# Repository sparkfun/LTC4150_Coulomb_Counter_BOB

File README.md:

SparkFun Coulomb Counter Breakout - LTC4150
===========================

[![SparkFun Coulomb Counter Breakout - LTC4150
](https://cdn.sparkfun.com//assets/parts/8/6/3/7/12052-01.jpg)](https://www.sparkfun.com/products/12052)

_[SparkFun Coulomb Counter Breakout - LTC4150 [ BOB-12052 ]](https://www.sparkfun.com/products/12052)_

*Breakout board for the Linear Tech LTC4150 Coulomb Counter (bidirectional current sensor / battery gauge)*

The LTC4150 Coulomb Counter monitors current passing through it (from the IN header or JST connector to the OUT header). Each time 0.1707 mAh passes through the device, the INT pin will pulse low. Or to put it another way, the INT pin will pulse low 5859 times for each Ah that passes through it.

There is also a POL pin that you can check each time INT goes low. POL will be L for current going from IN to OUT, and H for current going from OUT to IN (battery charging).

If you count these pulses and add or subtract from a total depending on the POL signal, you can keep accurate track of the state of a battery connected to the board.

The Coulomb Counter can accommodate power supplies up to 8.5V and up to 1A.

Quickstart (Arduino)
-------------------

* Configure the jumpers:

    If you're connecting the Coulomb Counter to a 5V system, leave solder jumpers SJ2 and SJ3 (on the bottom of the board) open (the default).

    If you're connecting the Coulomb Counter to a 3.3V system, close both SJ2 and SJ3.

* Hook up the I/O lines:

    Connect VIO to your system's VCC (3.3V or 5V) line.

    Connect GND to your system's ground line.

    Connect INT to your system's interrupt input (D3)

    Connect POL to an I/O pin (D4)

* Connect the IN header or the JST connector to your power source (up to 8.5V)

* Connect the OUT header to your system's power input

* Upload and run the Coulomb_Interrupt example code from this repository, and open a Serial Monitor set to 9600 bps. It should display a hello message and begin giving you periodic updates about the battery state. (See the comments for instructions on customizing it for your exact battery.)

See the [Hookup Guide](https://learn.sparkfun.com/tutorials/ltc4150-coulomb-counter-hookup-guide) for much more information.

Have fun! -Your friends at SparkFun

Repository Contents
-------------------

* **/Documentation** - Data sheets, additional product information
* **/Hardware** - Eagle design files (.brd, .sch)
* **/Production** - Production panel files (.brd)
* **/Software** - Arduino example code

Documentation
--------------

* **[Hookup Guide](https://learn.sparkfun.com/tutorials/ltc4150-coulomb-counter-hookup-guide)** - Basic hookup guide

License Information
-------------------

This product is _**open source**_! 

Please review the LICENSE.md file for license information. 

If you have any questions or concerns on licensing, please contact technical support on our [SparkFun forums](https://forum.sparkfun.com/viewforum.php?f=152).

Distributed as-is; no warranty is given.

- Your friends at SparkFun.

_<COLLABORATION CREDIT>_

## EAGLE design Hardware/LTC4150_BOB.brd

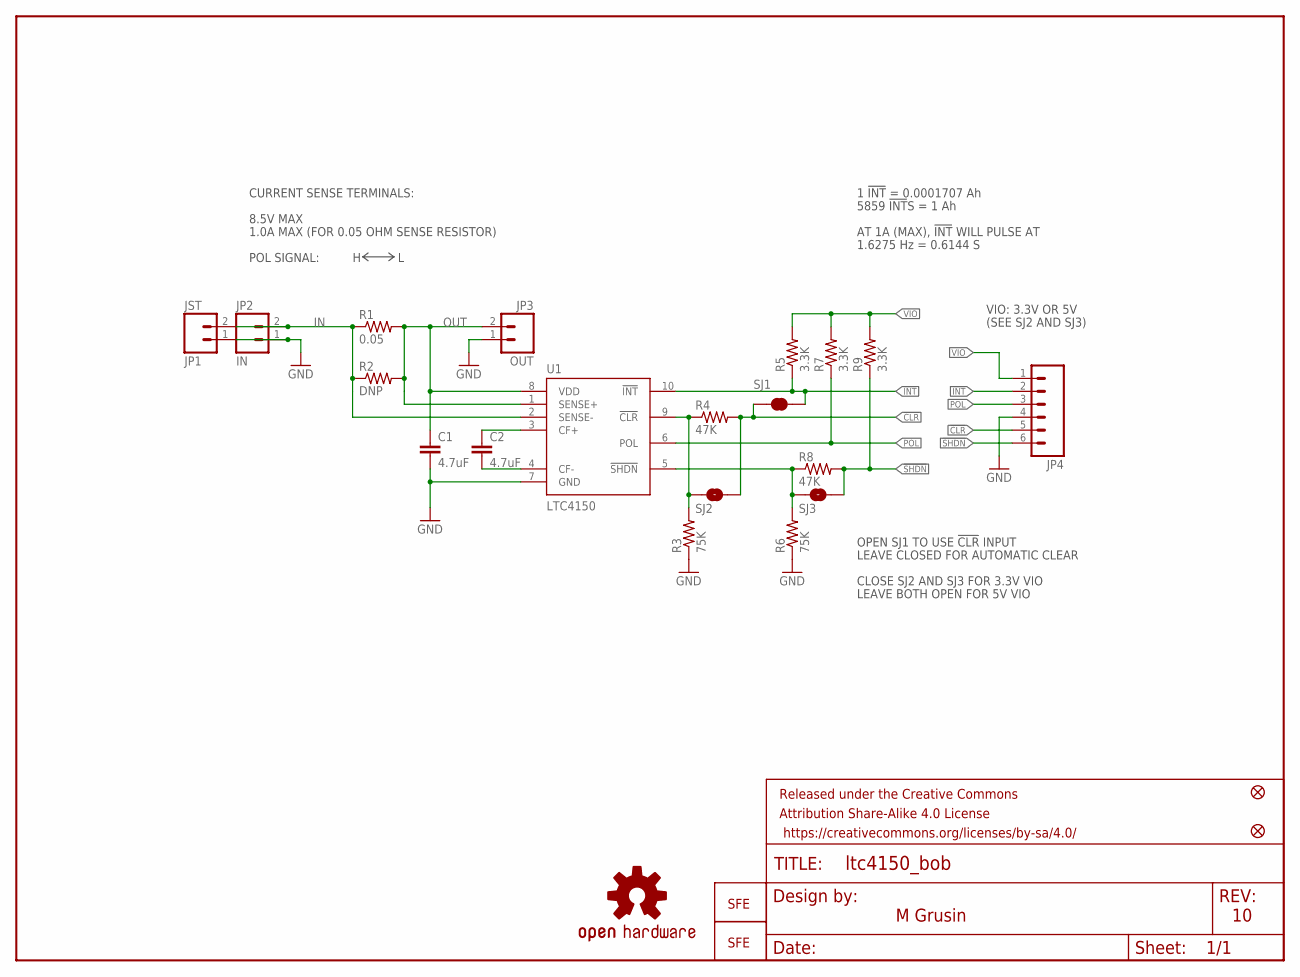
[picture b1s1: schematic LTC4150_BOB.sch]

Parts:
C1, C2: 4.7uF; 0603-CAP
FID1, FID2: FIDUCIAL1X2; FIDUCIAL-1X2
FRAME1: FRAME-LETTER; CREATIVE_COMMONS
JP1: JST; JST-2-SMD
JP2: IN; 1X02
JP3: OUT; 1X02
JP4: M06SIP; 1X06
LOGO1: OSHW-LOGOS; OSHW-LOGO-S
LOGO2: LOGO-SFENW2; SFE-NEW-WEB
LOGO3: LOGO-SFESK; SFE-LOGO-FLAME
R1: 0.05; 1206
R2: DNP; AXIAL-0.3
R3, R6: 75K; 0603-RES
R4, R8: 47K; 0603-RES
R5, R7, R9: 3.3K; 0603-RES
SJ1: SOLDERJUMPERNC; SJ_2S
SJ2, SJ3: SOLDERJUMPERNO; SJ_2S-NO
U1: LTC4150; MSOP10

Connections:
!CLR!: JP4.5, R4.2, SJ1.1, SJ2.2
!INT!: JP4.2, R5.1, SJ1.2, U1.10 (!INT!)
!SHDN!: JP4.6, R8.2, R9.1, SJ3.2
GND: C1.2, JP1.1 (2), JP2.1, JP3.1, JP4.4, R3.1, R6.1, U1.7 (GND)
IN: JP1.2 (1), JP2.2, R1.1, R2.P$1 (1), U1.2 (SENSE-)
unnamed: R3.2, R4.1, SJ2.1, U1.9 (!CLR!)
unnamed: C2.1, U1.3 (CF+)
unnamed: C2.2, U1.4 (CF-)
unnamed: R6.2, R8.1, SJ3.1, U1.5 (!SHDN!)
OUT: C1.1, JP3.2, R1.2, R2.P$2 (2), U1.1 (SENSE+), U1.8 (VDD)
POL: JP4.3, R7.1, U1.6 (POL)
VIO: JP4.1, R5.2, R7.2, R9.2

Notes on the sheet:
M Grusin
CLOSE SJ2 AND SJ3 FOR 3.3V VIO
CURRENT SENSE TERMINALS:
LEAVE BOTH OPEN FOR 5V VIO
AT 1A (MAX), !INT! WILL PULSE AT
1.6275 Hz = 0.6144 S
1 !INT! = 0.0001707 Ah
5859 !INT!S = 1 Ah
OPEN SJ1 TO USE !CLR! INPUT
1.0A MAX (FOR 0.05 OHM SENSE RESISTOR)
VIO: 3.3V OR 5V
(SEE SJ2 AND SJ3)
LEAVE CLOSED FOR AUTOMATIC CLEAR
8.5V MAX
POL SIGNAL:

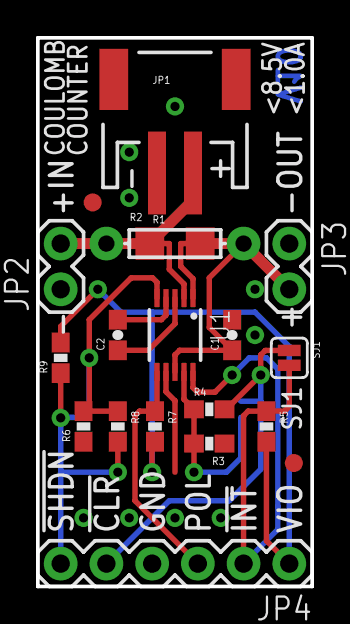
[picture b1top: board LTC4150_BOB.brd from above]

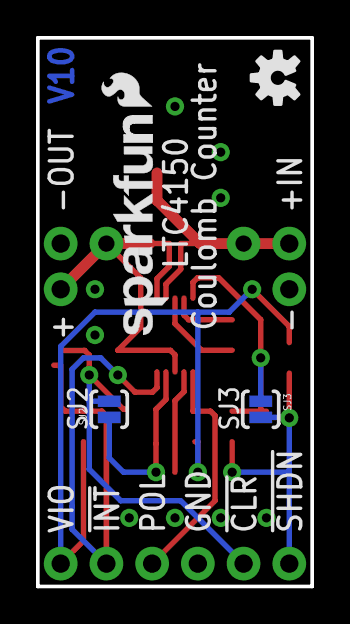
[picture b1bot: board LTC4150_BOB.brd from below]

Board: 2 copper layers, 15.2 x 30.5 mm, 25 parts (5 on the bottom side), 12 nets.

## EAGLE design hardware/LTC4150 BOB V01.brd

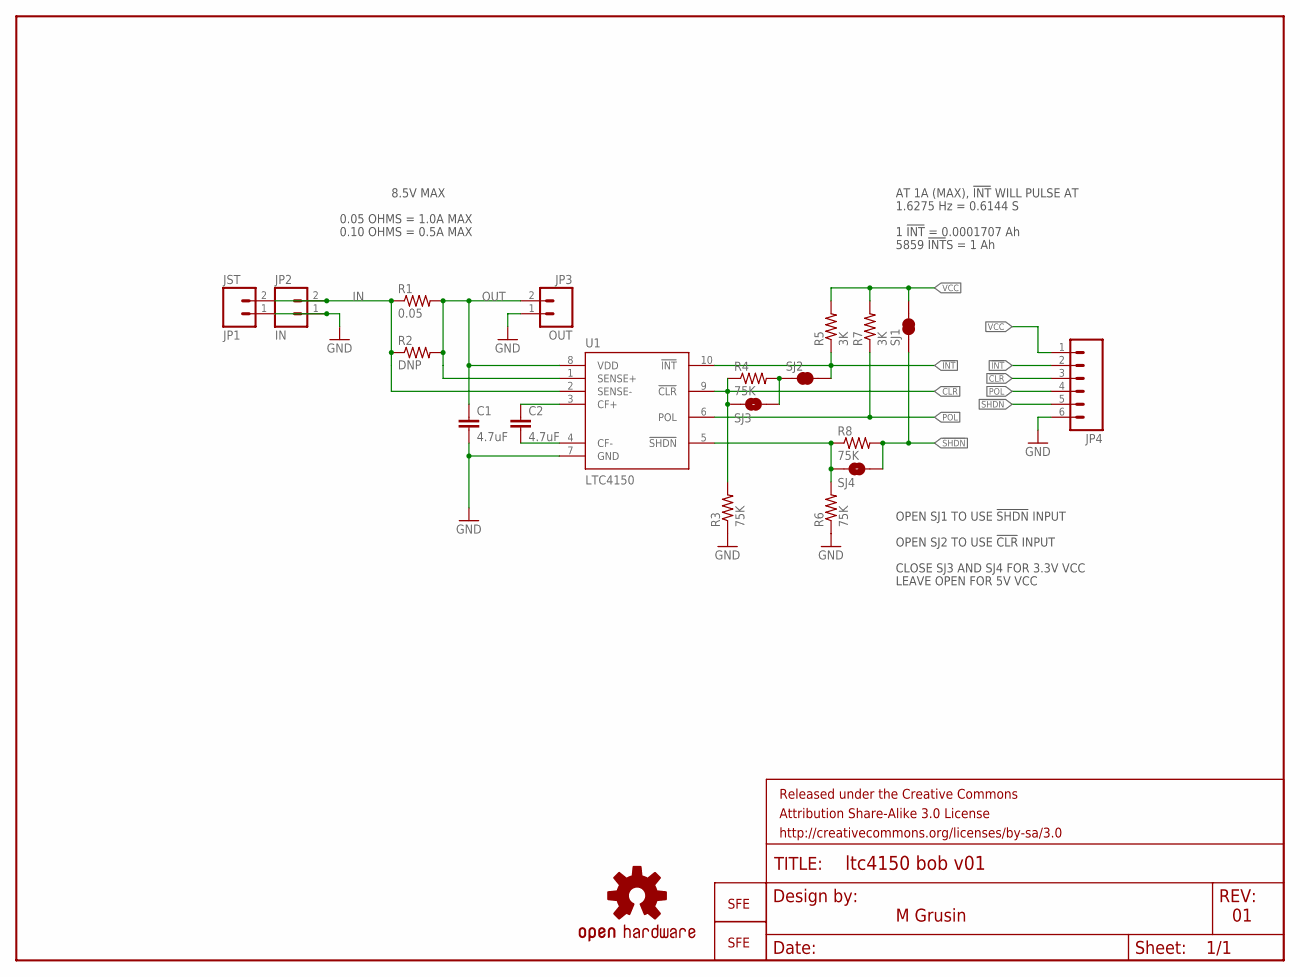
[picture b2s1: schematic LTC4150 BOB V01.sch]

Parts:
C1, C2: 4.7uF; 0603-CAP
FRAME1: FRAME-LETTER; CREATIVE_COMMONS
JP1: JST; JST-2-SMD
JP2: IN; 1X02
JP3: OUT; 1X02
JP4: M06SIP; 1X06
LOGO1: OSHW-LOGOS; OSHW-LOGO-S
LOGO2: LOGO-SFENW2; SFE-NEW-WEB
LOGO3: LOGO-SFESK; SFE-LOGO-FLAME
R1: 0.05; 0805
R2: DNP; AXIAL-0.3
R3, R4, R6, R8: 75K; 0603-RES
R5, R7: 3K; 0603-RES
SJ1, SJ2: SOLDERJUMPERNC; SJ_2S
SJ3, SJ4: SOLDERJUMPERNO; SJ_2S-NO
U1: LTC4150; MSOP10

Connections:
!CLR!: JP4.3, R3.2, R4.1, SJ3.1, U1.9 (!CLR!)
!INT!: JP4.2, R5.1, SJ2.2, U1.10 (!INT!)
!SHDN!: JP4.5, R8.2, SJ1.2, SJ4.2
GND: C1.2, JP1.1 (2), JP2.1, JP3.1, JP4.6, R3.1, R6.1, U1.7 (GND)
IN: JP1.2 (1), JP2.2, R1.1, R2.P$1 (1), U1.2 (SENSE-)
unnamed: R4.2, SJ2.1, SJ3.2
unnamed: C2.1, U1.3 (CF+)
unnamed: C2.2, U1.4 (CF-)
unnamed: R6.2, R8.1, SJ4.1, U1.5 (!SHDN!)
OUT: C1.1, JP3.2, R1.2, R2.P$2 (2), U1.1 (SENSE+), U1.8 (VDD)
POL: JP4.4, R7.1, U1.6 (POL)
VCC: JP4.1, R5.2, R7.2, SJ1.1

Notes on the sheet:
M Grusin
CLOSE SJ3 AND SJ4 FOR 3.3V VCC
OPEN SJ1 TO USE !SHDN! INPUT
8.5V MAX
LEAVE OPEN FOR 5V VCC
AT 1A (MAX), !INT! WILL PULSE AT
1.6275 Hz = 0.6144 S
1 !INT! = 0.0001707 Ah
5859 !INT!S = 1 Ah
OPEN SJ2 TO USE !CLR! INPUT
0.05 OHMS = 1.0A MAX
0.10 OHMS = 0.5A MAX

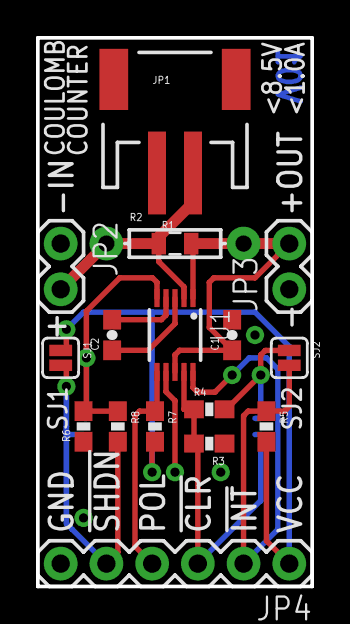
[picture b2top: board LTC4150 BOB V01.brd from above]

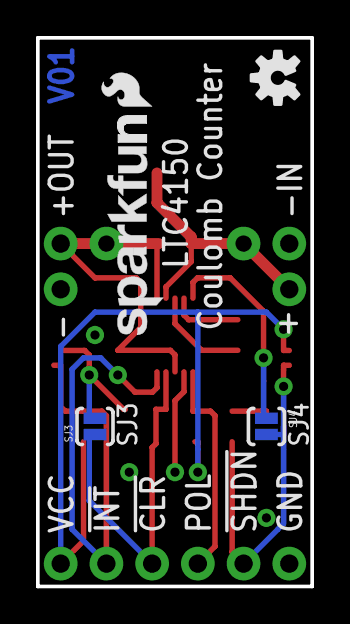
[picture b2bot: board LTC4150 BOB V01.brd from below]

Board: 2 copper layers, 15.2 x 30.5 mm, 23 parts (5 on the bottom side), 12 nets.

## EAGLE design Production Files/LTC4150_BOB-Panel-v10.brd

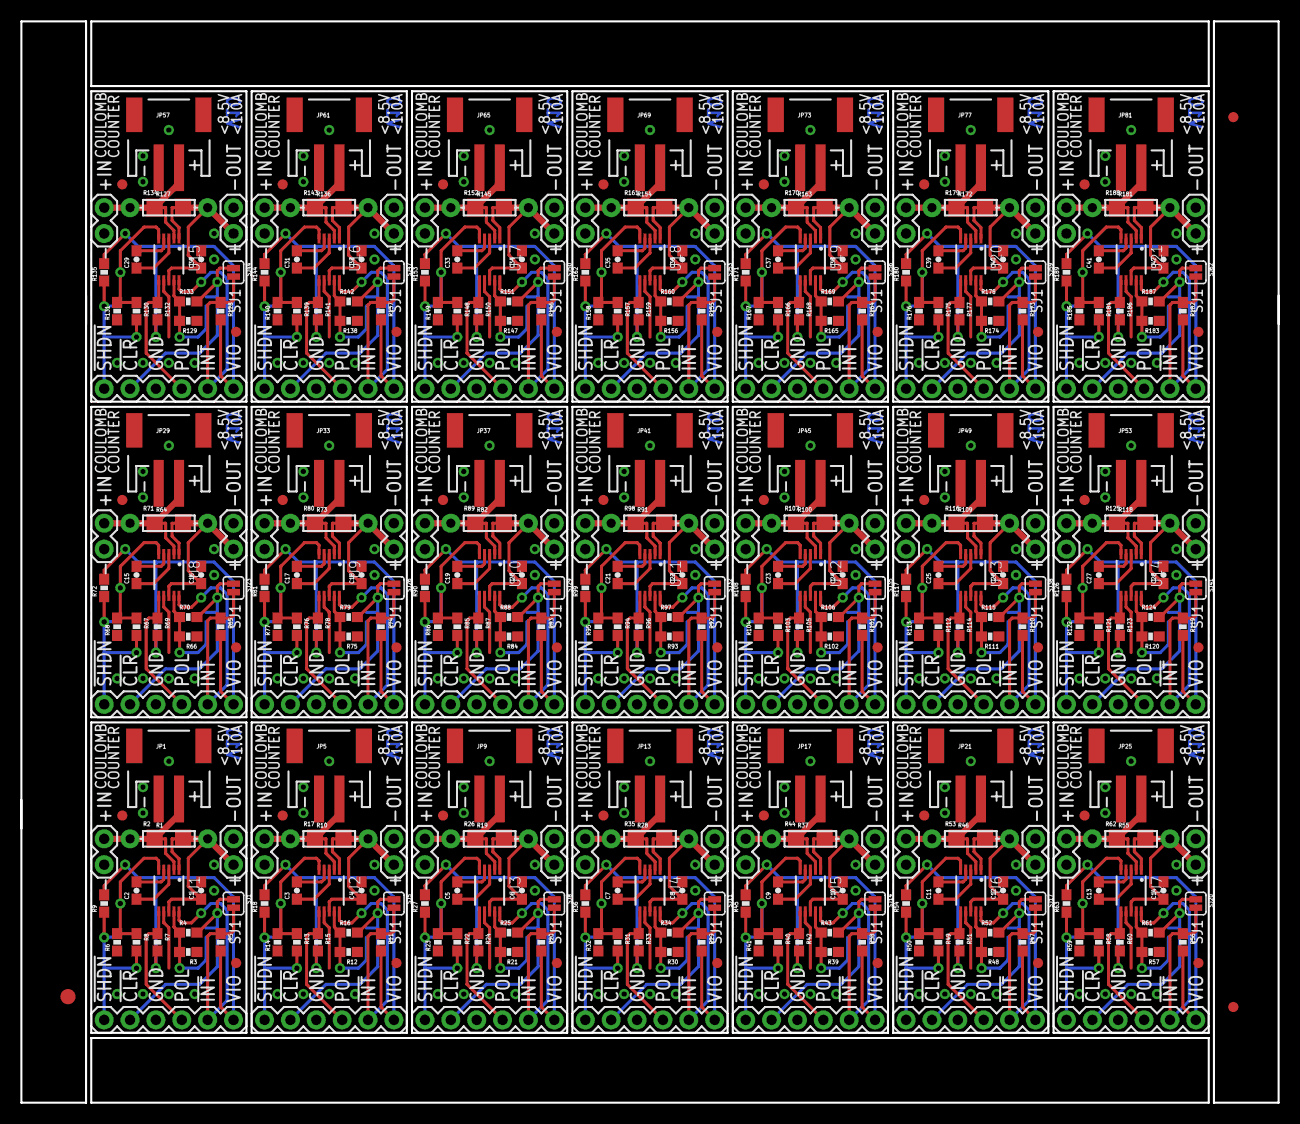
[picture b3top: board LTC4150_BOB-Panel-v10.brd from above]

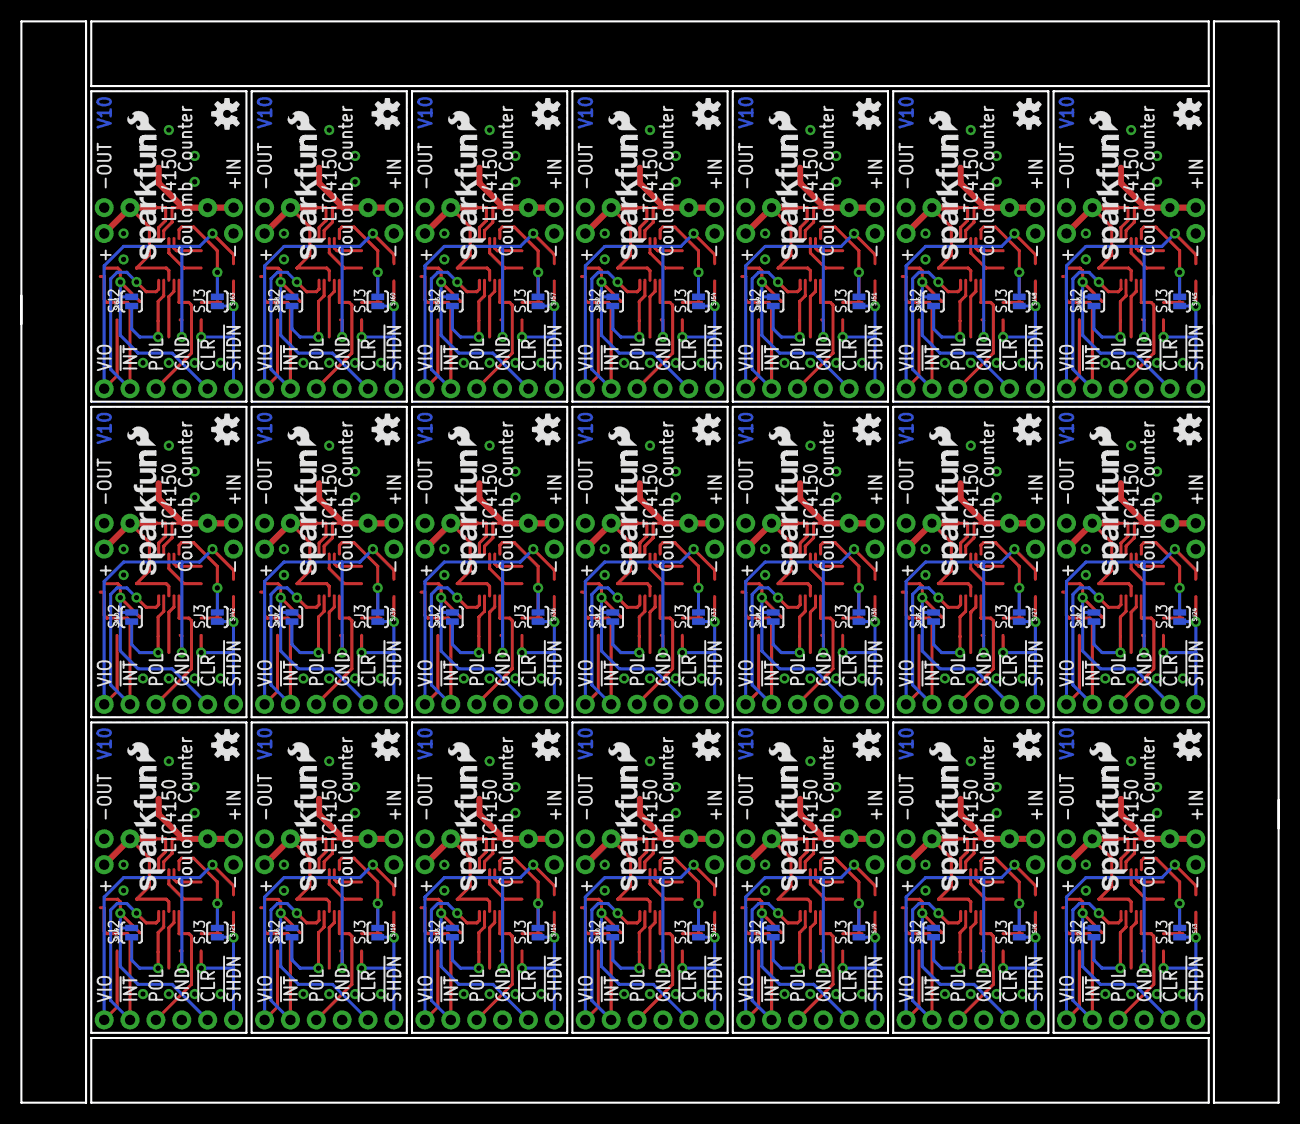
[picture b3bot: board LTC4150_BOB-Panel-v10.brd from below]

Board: 2 copper layers, 123.4 x 106.2 mm, 507 parts (105 on the bottom side), 252 nets.

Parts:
C1, C2, C3, C4, C5, C6, C7, C8, C9, C10, C11, C12, C13, C14, C15, C16, C17, C18, C19, C20, C21, C22, C23, C24, C25, C26, C27, C28, C29, C30, C31, C32, C33, C34, C35, C36, C37, C38, C39, C40, C41, C42: 4.7uF; 0603-CAP
E$1: FIDUCIAL-1.5X3
E$4, E$5: FIDUCIAL-1X2
FID1, FID2, FID3, FID4, FID5, FID6, FID7, FID8, FID9, FID10, FID11, FID12, FID13, FID14, FID15, FID16, FID17, FID18, FID19, FID20, FID21, FID22, FID23, FID24, FID25, FID26, FID27, FID28, FID29, FID30, FID31, FID32, FID33, FID34, FID35, FID36, FID37, FID38, FID39, FID40, FID41, FID42: FIDUCIAL1X2; FIDUCIAL-1X2
JP1, JP5, JP9, JP13, JP17, JP21, JP25, JP29, JP33, JP37, JP41, JP45, JP49, JP53, JP57, JP61, JP65, JP69, JP73, JP77, JP81: JST; JST-2-SMD
JP2, JP6, JP10, JP14, JP18, JP22, JP26, JP30, JP34, JP38, JP42, JP46, JP50, JP54, JP58, JP62, JP66, JP70, JP74, JP78, JP82: IN; 1X02
JP3, JP7, JP11, JP15, JP19, JP23, JP27, JP31, JP35, JP39, JP43, JP47, JP51, JP55, JP59, JP63, JP67, JP71, JP75, JP79, JP83: OUT; 1X02
JP4, JP8, JP12, JP16, JP20, JP24, JP28, JP32, JP36, JP40, JP44, JP48, JP52, JP56, JP60, JP64, JP68, JP72, JP76, JP80, JP84: 1X06
LOGO1, LOGO5, LOGO8, LOGO11, LOGO14, LOGO17, LOGO20, LOGO23, LOGO26, LOGO29, LOGO32, LOGO35, LOGO38, LOGO41, LOGO44, LOGO47, LOGO50, LOGO53, LOGO56, LOGO59, LOGO62: OSHW-LOGOS; OSHW-LOGO-S
LOGO2, LOGO6, LOGO9, LOGO12, LOGO15, LOGO18, LOGO21, LOGO24, LOGO27, LOGO30, LOGO33, LOGO36, LOGO39, LOGO42, LOGO45, LOGO48, LOGO51, LOGO54, LOGO57, LOGO60, LOGO63: LOGO-SFENW2; SFE-NEW-WEB
LOGO3, LOGO4, LOGO7, LOGO10, LOGO13, LOGO16, LOGO19, LOGO22, LOGO25, LOGO28, LOGO31, LOGO34, LOGO37, LOGO40, LOGO43, LOGO46, LOGO49, LOGO52, LOGO55, LOGO58, LOGO61: LOGO-SFESK; SFE-LOGO-FLAME
R1, R10, R19, R28, R37, R46, R55, R64, R73, R82, R91, R100, R109, R118, R127, R136, R145, R154, R163, R172, R181: 0.05; 1206
R2, R17, R26, R35, R44, R53, R62, R71, R80, R89, R98, R107, R116, R125, R134, R143, R152, R161, R170, R179, R188: DNP; AXIAL-0.3
R3, R6, R12, R14, R21, R23, R30, R32, R39, R41, R48, R50, R57, R59, R66, R68, R75, R77, R84, R86, R93, R95, R102, R104, R111, R113, R120, R122, R129, R131, R138, R140, R147, R149, R156, R158, R165, R167, R174, R176, R183, R185: 75K; 0603-RES
R4, R8, R13, R16, R22, R25, R31, R34, R40, R43, R49, R52, R58, R61, R67, R70, R76, R79, R85, R88, R94, R97, R103, R106, R112, R115, R121, R124, R130, R133, R139, R142, R148, R151, R157, R160, R166, R169, R175, R178, R184, R187: 47K; 0603-RES
R5, R7, R9, R11, R15, R18, R20, R24, R27, R29, R33, R36, R38, R42, R45, R47, R51, R54, R56, R60, R63, R65, R69, R72, R74, R78, R81, R83, R87, R90, R92, R96, R99, R101, R105, R108, R110, R114, R117, R119, R123, R126, R128, R132, R135, R137, R141, R144, R146, R150, R153, R155, R159, R162, R164, R168, R171, R173, R177, R180, R182, R186, R189: 3.3K; 0603-RES
SJ1, SJ5, SJ8, SJ11, SJ14, SJ17, SJ20, SJ23, SJ26, SJ29, SJ32, SJ35, SJ38, SJ41, SJ44, SJ47, SJ50, SJ53, SJ56, SJ59, SJ62: SJ_2S
SJ2, SJ3, SJ4, SJ6, SJ7, SJ9, SJ10, SJ12, SJ13, SJ15, SJ16, SJ18, SJ19, SJ21, SJ22, SJ24, SJ25, SJ27, SJ28, SJ30, SJ31, SJ33, SJ34, SJ36, SJ37, SJ39, SJ40, SJ42, SJ43, SJ45, SJ46, SJ48, SJ49, SJ51, SJ52, SJ54, SJ55, SJ57, SJ58, SJ60, SJ61, SJ63: SJ_2S-NO
U1, U2, U3, U4, U5, U6, U7, U8, U9, U10, U11, U12, U13, U14, U15, U16, U17, U18, U19, U20, U21: LTC4150; MSOP10

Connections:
!CLR!: JP4.5, R4.2, SJ1.1, SJ2.2
!CLR!1: JP8.5, R16.2, SJ4.2, SJ5.1
!CLR!2: JP12.5, R25.2, SJ7.2, SJ8.1
!CLR!3: JP16.5, R34.2, SJ10.2, SJ11.1
!CLR!4: JP20.5, R43.2, SJ13.2, SJ14.1
!CLR!5: JP24.5, R52.2, SJ16.2, SJ17.1
!CLR!6: JP28.5, R61.2, SJ19.2, SJ20.1
!CLR!7: JP32.5, R70.2, SJ22.2, SJ23.1
!CLR!8: JP36.5, R79.2, SJ25.2, SJ26.1
!CLR!9: JP40.5, R88.2, SJ28.2, SJ29.1
!CLR!10: JP44.5, R97.2, SJ31.2, SJ32.1
!CLR!11: JP48.5, R106.2, SJ34.2, SJ35.1
!CLR!12: JP52.5, R115.2, SJ37.2, SJ38.1
!CLR!13: JP56.5, R124.2, SJ40.2, SJ41.1
!CLR!14: JP60.5, R133.2, SJ43.2, SJ44.1
!CLR!15: JP64.5, R142.2, SJ46.2, SJ47.1
!CLR!16: JP68.5, R151.2, SJ49.2, SJ50.1
!CLR!17: JP72.5, R160.2, SJ52.2, SJ53.1
!CLR!18: JP76.5, R169.2, SJ55.2, SJ56.1
!CLR!19: JP80.5, R178.2, SJ58.2, SJ59.1
!CLR!20: JP84.5, R187.2, SJ61.2, SJ62.1
!INT!: JP4.2, R5.1, SJ1.2, U1.10
!INT!1: JP8.2, R11.1, SJ5.2, U2.10
!INT!2: JP12.2, R20.1, SJ8.2, U3.10
!INT!3: JP16.2, R29.1, SJ11.2, U4.10
!INT!4: JP20.2, R38.1, SJ14.2, U5.10
!INT!5: JP24.2, R47.1, SJ17.2, U6.10
!INT!6: JP28.2, R56.1, SJ20.2, U7.10
!INT!7: JP32.2, R65.1, SJ23.2, U8.10
!INT!8: JP36.2, R74.1, SJ26.2, U9.10
!INT!9: JP40.2, R83.1, SJ29.2, U10.10
!INT!10: JP44.2, R92.1, SJ32.2, U11.10
!INT!11: JP48.2, R101.1, SJ35.2, U12.10
!INT!12: JP52.2, R110.1, SJ38.2, U13.10
!INT!13: JP56.2, R119.1, SJ41.2, U14.10
!INT!14: JP60.2, R128.1, SJ44.2, U15.10
!INT!15: JP64.2, R137.1, SJ47.2, U16.10
!INT!16: JP68.2, R146.1, SJ50.2, U17.10
!INT!17: JP72.2, R155.1, SJ53.2, U18.10
!INT!18: JP76.2, R164.1, SJ56.2, U19.10
!INT!19: JP80.2, R173.1, SJ59.2, U20.10
!INT!20: JP84.2, R182.1, SJ62.2, U21.10
!SHDN!: JP4.6, R8.2, R9.1, SJ3.2
!SHDN!1: JP8.6, R13.2, R18.1, SJ6.2
!SHDN!2: JP12.6, R22.2, R27.1, SJ9.2
!SHDN!3: JP16.6, R31.2, R36.1, SJ12.2
!SHDN!4: JP20.6, R40.2, R45.1, SJ15.2
!SHDN!5: JP24.6, R49.2, R54.1, SJ18.2
!SHDN!6: JP28.6, R58.2, R63.1, SJ21.2
!SHDN!7: JP32.6, R67.2, R72.1, SJ24.2
!SHDN!8: JP36.6, R76.2, R81.1, SJ27.2
!SHDN!9: JP40.6, R85.2, R90.1, SJ30.2
!SHDN!10: JP44.6, R94.2, R99.1, SJ33.2
!SHDN!11: JP48.6, R103.2, R108.1, SJ36.2
!SHDN!12: JP52.6, R112.2, R117.1, SJ39.2
!SHDN!13: JP56.6, R121.2, R126.1, SJ42.2
!SHDN!14: JP60.6, R130.2, R135.1, SJ45.2
!SHDN!15: JP64.6, R139.2, R144.1, SJ48.2
!SHDN!16: JP68.6, R148.2, R153.1, SJ51.2
!SHDN!17: JP72.6, R157.2, R162.1, SJ54.2
!SHDN!18: JP76.6, R166.2, R171.1, SJ57.2
!SHDN!19: JP80.6, R175.2, R180.1, SJ60.2
!SHDN!20: JP84.6, R184.2, R189.1, SJ63.2
GND: C1.2, JP1.1, JP2.1, JP3.1, JP4.4, R3.1, R6.1, U1.7
GND1: C4.2, JP5.1, JP6.1, JP7.1, JP8.4, R12.1, R14.1, U2.7
GND2: C6.2, JP9.1, JP10.1, JP11.1, JP12.4, R21.1, R23.1, U3.7
GND3: C8.2, JP13.1, JP14.1, JP15.1, JP16.4, R30.1, R32.1, U4.7
GND4: C10.2, JP17.1, JP18.1, JP19.1, JP20.4, R39.1, R41.1, U5.7
GND5: C12.2, JP21.1, JP22.1, JP23.1, JP24.4, R48.1, R50.1, U6.7
GND6: C14.2, JP25.1, JP26.1, JP27.1, JP28.4, R57.1, R59.1, U7.7
GND7: C16.2, JP29.1, JP30.1, JP31.1, JP32.4, R66.1, R68.1, U8.7
GND8: C18.2, JP33.1, JP34.1, JP35.1, JP36.4, R75.1, R77.1, U9.7
GND9: C20.2, JP37.1, JP38.1, JP39.1, JP40.4, R84.1, R86.1, U10.7
GND10: C22.2, JP41.1, JP42.1, JP43.1, JP44.4, R93.1, R95.1, U11.7
GND11: C24.2, JP45.1, JP46.1, JP47.1, JP48.4, R102.1, R104.1, U12.7
GND12: C26.2, JP49.1, JP50.1, JP51.1, JP52.4, R111.1, R113.1, U13.7
GND13: C28.2, JP53.1, JP54.1, JP55.1, JP56.4, R120.1, R122.1, U14.7
GND14: C30.2, JP57.1, JP58.1, JP59.1, JP60.4, R129.1, R131.1, U15.7
GND15: C32.2, JP61.1, JP62.1, JP63.1, JP64.4, R138.1, R140.1, U16.7
GND16: C34.2, JP65.1, JP66.1, JP67.1, JP68.4, R147.1, R149.1, U17.7
GND17: C36.2, JP69.1, JP70.1, JP71.1, JP72.4, R156.1, R158.1, U18.7
GND18: C38.2, JP73.1, JP74.1, JP75.1, JP76.4, R165.1, R167.1, U19.7
GND19: C40.2, JP77.1, JP78.1, JP79.1, JP80.4, R174.1, R176.1, U20.7
GND20: C42.2, JP81.1, JP82.1, JP83.1, JP84.4, R183.1, R185.1, U21.7
IN: JP1.2, JP2.2, R1.1, R2.P$1, U1.2
IN1: JP5.2, JP6.2, R10.1, R17.P$1, U2.2
IN2: JP9.2, JP10.2, R19.1, R26.P$1, U3.2
IN3: JP13.2, JP14.2, R28.1, R35.P$1, U4.2
IN4: JP17.2, JP18.2, R37.1, R44.P$1, U5.2
IN5: JP21.2, JP22.2, R46.1, R53.P$1, U6.2
IN6: JP25.2, JP26.2, R55.1, R62.P$1, U7.2
IN7: JP29.2, JP30.2, R64.1, R71.P$1, U8.2
IN8: JP33.2, JP34.2, R73.1, R80.P$1, U9.2
IN9: JP37.2, JP38.2, R82.1, R89.P$1, U10.2
IN10: JP41.2, JP42.2, R91.1, R98.P$1, U11.2
IN11: JP45.2, JP46.2, R100.1, R107.P$1, U12.2
IN12: JP49.2, JP50.2, R109.1, R116.P$1, U13.2
IN13: JP53.2, JP54.2, R118.1, R125.P$1, U14.2
IN14: JP57.2, JP58.2, R127.1, R134.P$1, U15.2
IN15: JP61.2, JP62.2, R136.1, R143.P$1, U16.2
IN16: JP65.2, JP66.2, R145.1, R152.P$1, U17.2
IN17: JP69.2, JP70.2, R154.1, R161.P$1, U18.2
IN18: JP73.2, JP74.2, R163.1, R170.P$1, U19.2
IN19: JP77.2, JP78.2, R172.1, R179.P$1, U20.2
IN20: JP81.2, JP82.2, R181.1, R188.P$1, U21.2
unnamed: R3.2, R4.1, SJ2.1, U1.9
unnamed: C3.1, U2.3
unnamed: C2.1, U1.3
unnamed: C2.2, U1.4
unnamed: C3.2, U2.4
unnamed: R13.1, R14.2, SJ6.1, U2.5
unnamed: R12.2, R16.1, SJ4.1, U2.9
unnamed: C5.1, U3.3
unnamed: R6.2, R8.1, SJ3.1, U1.5
unnamed: C5.2, U3.4
unnamed: R22.1, R23.2, SJ9.1, U3.5
unnamed: R21.2, R25.1, SJ7.1, U3.9
unnamed: C7.1, U4.3
unnamed: C7.2, U4.4
unnamed: R31.1, R32.2, SJ12.1, U4.5
unnamed: R30.2, R34.1, SJ10.1, U4.9
unnamed: C9.1, U5.3
unnamed: C9.2, U5.4
unnamed: R40.1, R41.2, SJ15.1, U5.5
unnamed: R39.2, R43.1, SJ13.1, U5.9
unnamed: C11.1, U6.3
unnamed: C11.2, U6.4
unnamed: R49.1, R50.2, SJ18.1, U6.5
unnamed: R48.2, R52.1, SJ16.1, U6.9
unnamed: C13.1, U7.3
unnamed: C13.2, U7.4
unnamed: R58.1, R59.2, SJ21.1, U7.5
unnamed: R57.2, R61.1, SJ19.1, U7.9
unnamed: C15.1, U8.3
unnamed: C15.2, U8.4
unnamed: R67.1, R68.2, SJ24.1, U8.5
unnamed: R66.2, R70.1, SJ22.1, U8.9
unnamed: C17.1, U9.3
unnamed: C17.2, U9.4
unnamed: R76.1, R77.2, SJ27.1, U9.5
unnamed: R75.2, R79.1, SJ25.1, U9.9
unnamed: C19.1, U10.3
unnamed: C19.2, U10.4
unnamed: R85.1, R86.2, SJ30.1, U10.5
unnamed: R84.2, R88.1, SJ28.1, U10.9
unnamed: C21.1, U11.3
unnamed: C21.2, U11.4
unnamed: R94.1, R95.2, SJ33.1, U11.5
unnamed: R93.2, R97.1, SJ31.1, U11.9
unnamed: C23.1, U12.3
unnamed: C23.2, U12.4
unnamed: R103.1, R104.2, SJ36.1, U12.5
unnamed: R102.2, R106.1, SJ34.1, U12.9
unnamed: C25.1, U13.3
unnamed: C25.2, U13.4
unnamed: R112.1, R113.2, SJ39.1, U13.5
unnamed: R111.2, R115.1, SJ37.1, U13.9
unnamed: C27.1, U14.3
unnamed: C27.2, U14.4
unnamed: R121.1, R122.2, SJ42.1, U14.5
unnamed: R120.2, R124.1, SJ40.1, U14.9
unnamed: C29.1, U15.3
unnamed: C29.2, U15.4
unnamed: R130.1, R131.2, SJ45.1, U15.5
unnamed: R129.2, R133.1, SJ43.1, U15.9
unnamed: C31.1, U16.3
unnamed: C31.2, U16.4
unnamed: R139.1, R140.2, SJ48.1, U16.5
unnamed: R138.2, R142.1, SJ46.1, U16.9
unnamed: C33.1, U17.3
unnamed: C33.2, U17.4
unnamed: R148.1, R149.2, SJ51.1, U17.5
unnamed: R147.2, R151.1, SJ49.1, U17.9
unnamed: C35.1, U18.3
unnamed: C35.2, U18.4
unnamed: R157.1, R158.2, SJ54.1, U18.5
unnamed: R156.2, R160.1, SJ52.1, U18.9
unnamed: C37.1, U19.3
unnamed: C37.2, U19.4
unnamed: R166.1, R167.2, SJ57.1, U19.5
unnamed: R165.2, R169.1, SJ55.1, U19.9
unnamed: C39.1, U20.3
unnamed: C39.2, U20.4
unnamed: R175.1, R176.2, SJ60.1, U20.5
unnamed: R174.2, R178.1, SJ58.1, U20.9
unnamed: C41.1, U21.3
unnamed: C41.2, U21.4
unnamed: R184.1, R185.2, SJ63.1, U21.5
unnamed: R183.2, R187.1, SJ61.1, U21.9
OUT: C1.1, JP3.2, R1.2, R2.P$2, U1.1, U1.8
OUT1: C4.1, JP7.2, R10.2, R17.P$2, U2.1, U2.8
OUT2: C6.1, JP11.2, R19.2, R26.P$2, U3.1, U3.8
OUT3: C8.1, JP15.2, R28.2, R35.P$2, U4.1, U4.8
OUT4: C10.1, JP19.2, R37.2, R44.P$2, U5.1, U5.8
OUT5: C12.1, JP23.2, R46.2, R53.P$2, U6.1, U6.8
OUT6: C14.1, JP27.2, R55.2, R62.P$2, U7.1, U7.8
OUT7: C16.1, JP31.2, R64.2, R71.P$2, U8.1, U8.8
OUT8: C18.1, JP35.2, R73.2, R80.P$2, U9.1, U9.8
OUT9: C20.1, JP39.2, R82.2, R89.P$2, U10.1, U10.8
OUT10: C22.1, JP43.2, R91.2, R98.P$2, U11.1, U11.8
OUT11: C24.1, JP47.2, R100.2, R107.P$2, U12.1, U12.8
OUT12: C26.1, JP51.2, R109.2, R116.P$2, U13.1, U13.8
OUT13: C28.1, JP55.2, R118.2, R125.P$2, U14.1, U14.8
OUT14: C30.1, JP59.2, R127.2, R134.P$2, U15.1, U15.8
OUT15: C32.1, JP63.2, R136.2, R143.P$2, U16.1, U16.8
OUT16: C34.1, JP67.2, R145.2, R152.P$2, U17.1, U17.8
OUT17: C36.1, JP71.2, R154.2, R161.P$2, U18.1, U18.8
OUT18: C38.1, JP75.2, R163.2, R170.P$2, U19.1, U19.8
OUT19: C40.1, JP79.2, R172.2, R179.P$2, U20.1, U20.8
OUT20: C42.1, JP83.2, R181.2, R188.P$2, U21.1, U21.8
POL: JP4.3, R7.1, U1.6
POL1: JP8.3, R15.1, U2.6
POL2: JP12.3, R24.1, U3.6
POL3: JP16.3, R33.1, U4.6
POL4: JP20.3, R42.1, U5.6
POL5: JP24.3, R51.1, U6.6
POL6: JP28.3, R60.1, U7.6
POL7: JP32.3, R69.1, U8.6
POL8: JP36.3, R78.1, U9.6
POL9: JP40.3, R87.1, U10.6
POL10: JP44.3, R96.1, U11.6
POL11: JP48.3, R105.1, U12.6
POL12: JP52.3, R114.1, U13.6
POL13: JP56.3, R123.1, U14.6
POL14: JP60.3, R132.1, U15.6
POL15: JP64.3, R141.1, U16.6
POL16: JP68.3, R150.1, U17.6
POL17: JP72.3, R159.1, U18.6
POL18: JP76.3, R168.1, U19.6
POL19: JP80.3, R177.1, U20.6
POL20: JP84.3, R186.1, U21.6
VIO: JP4.1, R5.2, R7.2, R9.2
VIO1: JP8.1, R11.2, R15.2, R18.2
VIO2: JP12.1, R20.2, R24.2, R27.2
VIO3: JP16.1, R29.2, R33.2, R36.2
VIO4: JP20.1, R38.2, R42.2, R45.2
VIO5: JP24.1, R47.2, R51.2, R54.2
VIO6: JP28.1, R56.2, R60.2, R63.2
VIO7: JP32.1, R65.2, R69.2, R72.2
VIO8: JP36.1, R74.2, R78.2, R81.2
VIO9: JP40.1, R83.2, R87.2, R90.2
VIO10: JP44.1, R92.2, R96.2, R99.2
VIO11: JP48.1, R101.2, R105.2, R108.2
VIO12: JP52.1, R110.2, R114.2, R117.2
VIO13: JP56.1, R119.2, R123.2, R126.2
VIO14: JP60.1, R128.2, R132.2, R135.2
VIO15: JP64.1, R137.2, R141.2, R144.2
VIO16: JP68.1, R146.2, R150.2, R153.2
VIO17: JP72.1, R155.2, R159.2, R162.2
VIO18: JP76.1, R164.2, R168.2, R171.2
VIO19: JP80.1, R173.2, R177.2, R180.2
VIO20: JP84.1, R182.2, R186.2, R189.2

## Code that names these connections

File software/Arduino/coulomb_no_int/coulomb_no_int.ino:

/* LTC4150 Coulomb Counter no-interrupt example code
Mike Grusin, SparkFun Electronics

This sketch shows how to use the LTC4150 Coulomb Counter breakout
board to implement a battery "gas gauge" without using interrupts.

Product page: https://www.sparkfun.com/products/12052
Software repository: https://github.com/sparkfun/LTC4150_Coulomb_Counter_BOB

HOW IT WORKS:

Battery capacity is measured in amp-hours (Ah). For example, a one
amp-hour battery can provide 1 amp of current for one hour, or 2 amps
for half an hour, or half an amp for two hours, etc.

The LTC4150 monitors current passing into or out of a battery.
It has an output called INT (interrupt) that will pulse low every
time 0.0001707 amp-hours passes through the part. Or to put it
another way, the INT signal will pulse 5859 times for one amp-hour.

If you hook up a full 1Ah (1000mAh) battery to the LTC4150, you
can expect to get 5859 pulses before it's depleted. If you keep track
of these pulses, you can accurately determine the remaining battery
capacity.

There is also a POL (polarity) signal coming out of the LTC4150.
When you detect a pulse, you can check the POL signal to see whether
current is moving into or out of the battery. If POL is low, current is
coming out of the battery (discharging). If POL is high, current is
going into the battery (charging).

(Note that because of chemical inefficiencies, it takes a bit more current
to charge a battery than you will eventually get out of it. This sketch
does not take this into account. For better accuracy you might provide
a method to "zero" a full battery, either automatically or manually.)

Although it isn't the primary function of the part, you can also
measure the time between pulses to calculate current draw. At 1A
(the maximum allowed), INT will pulse every 0.6144 seconds, or
1.6275 Hz. Note that for low currents, pulses will be many seconds
apart, so don't expect frequent updates.

There are two methods you can use to keep track of the INT pulses. You
can use an interrupt input to monitor the INT signal in the background,
or you can monitor the INT line yourself and use the CLR signal to reset
the LTC4150 for the next pulse.

** This sketch shows how to operate the LTC4150 without interrupts **

HARDWARE CONNECTIONS:

Before connecting this board to your Arduino, double check that
all three solder jumpers are set appropriately.

For this sketch, unsolder (open) SJ1.
This disconnects INT and CLR to allow you to use the CLR signal manually.

If you're using a 5V Arduino, leave both SJ2 and SJ3 open (unsoldered).

If you're using a 3.3V Arduino, close (solder) both SJ2 and SJ3.

Connect the following pins to your Arduino:

VIO to VCC
GND to GND
INT to D3
POL to D4
CLR to D6

Note that if you solder headers to the bottom of the board,
you can plug the breakout board directly into Arduino header
pins D2 (VIO) through D7 (SHDN).

RUNNING THE SKETCH:

This sketch monitors current moving into and out of a battery.
Whenever it detects a low INT signal from the LTC4150, it will
clear INT by making the CLR pin low, update the battery state-
of-charge (how full the battery is), current draw, etc.

The sketch is hardcoded for a 2000mAh battery that is 100% full
when the sketch starts. You can easily change this by editing
the following lines:

  double battery_mAh = 2000.0; // milliamp-hours (mAh)
  double battery_percent = 100.0;  // state-of-charge (percent)

After uploading the sketch, open the Serial Monitor and set the
baud rate to 9600. Whenever the sketch detects an INT pulse, it
will update its calculations and print them out.

LICENSE:

Our example code uses the "beerware" license. You can do anything
you like with this code. No really, anything. If you find it useful
and you meet one of us in person someday, consider buying us a beer.

Have fun! -Your friends at SparkFun.
*/

// For this sketch you only need the first five of the 
// following pins, but you can plug the board directly
// into the Arduino header (D2-D7) for convenience.

// (If you are not plugging the board directly into the
// header, you can remove all references to VIO, GND,
// and SHDN.)

#define VIO 2 // Just used for the HIGH reference voltage
#define INT 3
#define POL 4
#define GND 5 // Just used for the LOW reference voltage
#define CLR 6
#define SHDN 7 // Unneeded in this sketch, set to input

#define LED 13 // Standard Arduino LED

// Change the following two lines to match your battery
// and its initial state-of-charge:

double battery_mAh = 2000.0; // milliamp-hours (mAh)
double battery_percent = 100.0;  // state-of-charge (percent)

// Global variables:

double ah_quanta = 0.17067759; // mAh for each INT
double percent_quanta; // calculate below

void setup()
{
  // Set up I/O pins:
  
  pinMode(GND,OUTPUT);
  digitalWrite(GND,LOW);

  pinMode(VIO,OUTPUT);
  digitalWrite(VIO,HIGH);

  pinMode(INT,INPUT);

  pinMode(POL,INPUT);

  pinMode(CLR,OUTPUT);
  digitalWrite(CLR,HIGH);
  
  pinMode(SHDN,INPUT); // Unneeded, disabled by setting to input

  pinMode(LED,OUTPUT);
  digitalWrite(LED,LOW);  

  // Enable serial output:

  Serial.begin(9600);
  Serial.println("LTC4150 Coulomb Counter BOB no-interrupt example");

  // One INT is this many percent of battery capacity:
  
  percent_quanta = 1.0/(battery_mAh/1000.0*5859.0/100.0);
}

void loop()
{
  static long int time, lasttime;
  double mA;
  boolean polarity;

  if (digitalRead(INT)==0) // INT has gone low
  {
    // Determine delay since last interrupt (for mA calculation)
    // Note that first interrupt will be incorrect (no previous time!)

    lasttime = time;
    time = micros();

    // Get the polarity value
    
    polarity = digitalRead(POL);
    if (polarity) // high = charging
    {
      battery_mAh += ah_quanta;
      battery_percent += percent_quanta;
    }
    else // low = discharging
    {
      battery_mAh -= ah_quanta;
      battery_percent -= percent_quanta;
    }

    // Calculate mA from time delay (optional)
  
    mA = 614.4/((time-lasttime)/1000000.0);
  
    // If charging, we'll set mA negative (optional)
    
    if (polarity) mA = mA * -1.0;

    // Clear the interrupt signal

    digitalWrite(CLR,LOW);
    delayMicroseconds(40); // CLR needs to be low > 20us
    digitalWrite(CLR,HIGH);

    // Blink the LED (optional)
    
    digitalWrite(LED,HIGH);
    delay(100);
    digitalWrite(LED,LOW);

    // Print out the current battery status

    Serial.print("mAh: ");
    Serial.print(battery_mAh);
    Serial.print(" soc: ");
    Serial.print(battery_percent);
    Serial.print("% time: ");
    Serial.print((time-lasttime)/1000000.0);
    Serial.print("s mA: ");
    Serial.println(mA);
  }
}

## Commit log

2013-07-30 Ready for proto?
2013-09-06 V02 ready for prototype
2014-04-19 fixed silk error
2014-04-21 Final cleanup for reds
2014-04-21 fixed resistor layout for 5V operation
2014-05-01 Added initial example code
2014-05-02 Changed temp parts to SparkFun library variants
2014-05-02 Demo sketches in-progress
2014-06-07 Rename and rearrange repository
2014-06-07 Changed version to 1.0 for reds
2014-06-11 Replaced solder jumper with pullup resistor
2014-06-16 Cleanup example code
2014-06-16 Moar cleanup example code
2014-06-19 added board fiducials
2014-06-19 created panel v10
2014-09-11 updating code and tree
2014-09-11 updated 7-segment example
2014-09-15 Clean up 7-segment example code
2014-09-18 Updated README with product links
2014-09-18 Markdown tweaks
2014-09-18 still tweaking...
2014-09-18 maybe twerking?
2020-05-22 Adjust folders to be case-sensitive
2020-05-22 Delete Coulomb Counter 4150fc.pdf
    remove duplicate
2020-05-22 Delete LTC4150_BOB.pdf
    remove duplicate
2020-05-22 Delete spreadsheet.ods
    remove duplicate
2020-05-22 Delete LTC4150_BOB.brd
    remove duplicate
2020-05-22 Delete LTC4150_BOB.sch
    remove duplicate
2020-05-22 Delete coulomb_7seg.ino
    remove duplicate
2020-05-22 Delete coulomb_interrupt.ino
    remove duplicate
2020-05-22 Delete coulomb_polling.ino
    remove duplicate
2021-08-17 Update coulomb_interrupt.ino
    Actually using the INT pin variable, so that people using any pin other than D3 (or any other board than the 328 Arduinos) can specify their INT pin.

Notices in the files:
parts and their libraries:
SparkFun-Aesthetics: Licensing: CC v3.0 Share-Alike You are welcome to use this library for commercial purposes.
SparkFun-Aesthetics: Released under the Creative Commons Attribution Share-Alike 4.0 License
SparkFun-Aesthetics: https://creativecommons.org/licenses/by-sa/4.0
